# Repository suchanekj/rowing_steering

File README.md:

# Marine Steering System (Buccaneer)

This is a marine steering system designed to track and steer a boat during a rowing outing. It is made up of a cross-platform mobile app built in React Native, along with an Arduino-operated servo designed to control the boat's rudder and a game controller.

The system features three modes:

### 1. Tracking only

This mode tracks your outing without providing any sort of control. Simply line the phone up in the direction of the boat and it will record your outing and useful information like distance and average speed. Past outings can then be reviewed from the history tab.

### 2. Manual mode

In addition to tracking your outing, manual mode allows you to control the boat's rudder from a wireless game controller that can be kept in your hand whilst rowing. Simply connect the servo and controller to the app via bluetooth in the settings tab, and then select manual mode to enable.

### 3. Automatic mode

Lastly, the ultimate goal of the system is to enable fully automated steering. This is a achived by a simple PID controller. The boat's current heading is compared to an average of the river's bearing over the next 100m, weighted by proximity. This forms the error input to a PID controller, which provides a corrective rudder angle output. Simply connect the servo via bluetooth in the settings tab and select automatic mode to enable.

## Screenshots

## Running the app

The app has been built in React Native, a cross-platform framework for developing mobile apps using Javascript.

To work on the app, you'll need to set up a few tools that allow you to run the app on your iOS or Android device. For Android, this involves installing Node and Watchman, followed by the Java Development Kit and Android Studio. See the [docs](https://reactnative.dev/docs/environment-setup) for more details and also for instructions for iOS. Select "React Native CLI Quickstart" rather than "Expo CLI Quickstart". Expo is a set of tools that make React Native development easier, but sadly bluetooth functionality is not yet available in Expo, so we're following the ordinary React Native CLI workflow, sometimes called the "bare workflow".

Once the tools are set up, enable USB debugging on your Android device, connect it via USB and run:

```
npx react-native run-android
```

See the [docs](https://reactnative.dev/docs/running-on-device) for more details and also for instructions for iOS. They also provide [instructions](https://reactnative.dev/docs/signed-apk-android) on building an APK build of the app.

## To do

The functionality of the app is largely complete. It has been tested on Android and the tracking mode works well. The app also correctly scans for and picks up surrounding bluetooth devices. However, manual and automatic modes have yet to be tested in conjunction with the hardware.

In terms of hardware, the servo and game controller must be able to receive and send the following bluetooth messages from the phone:

All bluetooth messages consist of signed 8-bit integers. The servo receives from the phone a rudder angle between -90 and 90, and sends the phone a battery level between 0 and 100. The controller receives from the phone the servo's battery level between 0 and 100, and sends a change in rudder angle between -128 and 127. The phone will add this received value to the current rudder angle to determine the new rudder angle.

The following UUIDs are used for each message. Note that I've come up with new ones, so you'll have to replace the UUIDs used in the current servo code.

```
export const SERVO_SERICE = "802af24b-b40a-488b-b740-4c0405c1f955";
export const BATTERY_LEVEL_CHARACTERISTIC =
  "27468c1f-2915-4b5a-ac6a-6efb97dd764e"; // the servo to phone battery level message (0 to 100)
export const RUDDER_ANGLE_CHARACTERISTIC =
  "948c9983-d637-405b-be86-4565e3c0b7dd"; // the phone to servo rudder angle message (-90 to 90)

export const CONTROLLER_SERVICE = "8be2ecbd-047b-4af5-99fc-ad5a571a99c8";
export const RUDDER_CHANGE_CHARACTERISTIC =
  "1aa10f81-2712-4eb1-a4fc-6c2b0ba74671"; // the controller to phone rudder angle change message (-128 to 127)
export const BATTERY_INFO_CHARACTERISTIC =
  "3a7b1270-435a-4927-86fb-cd135bee2ca5"; // the phone to servo battery level message (0 to 100)

```

## Notes

### Bluetooth device names in the app

The bluetooth library the app uses currently has a bug. When you scan for nearby bluetooth devices, the discovered devices don't have names, only MAC ID addresses. Hopefully this will be fixed in a future release, but for now the app displays the MAC ID addresses of possible devices instead of their names. This isn't ideal but if you keep a note of the MAC ID address of the servo and controller you can connect to the right devices.

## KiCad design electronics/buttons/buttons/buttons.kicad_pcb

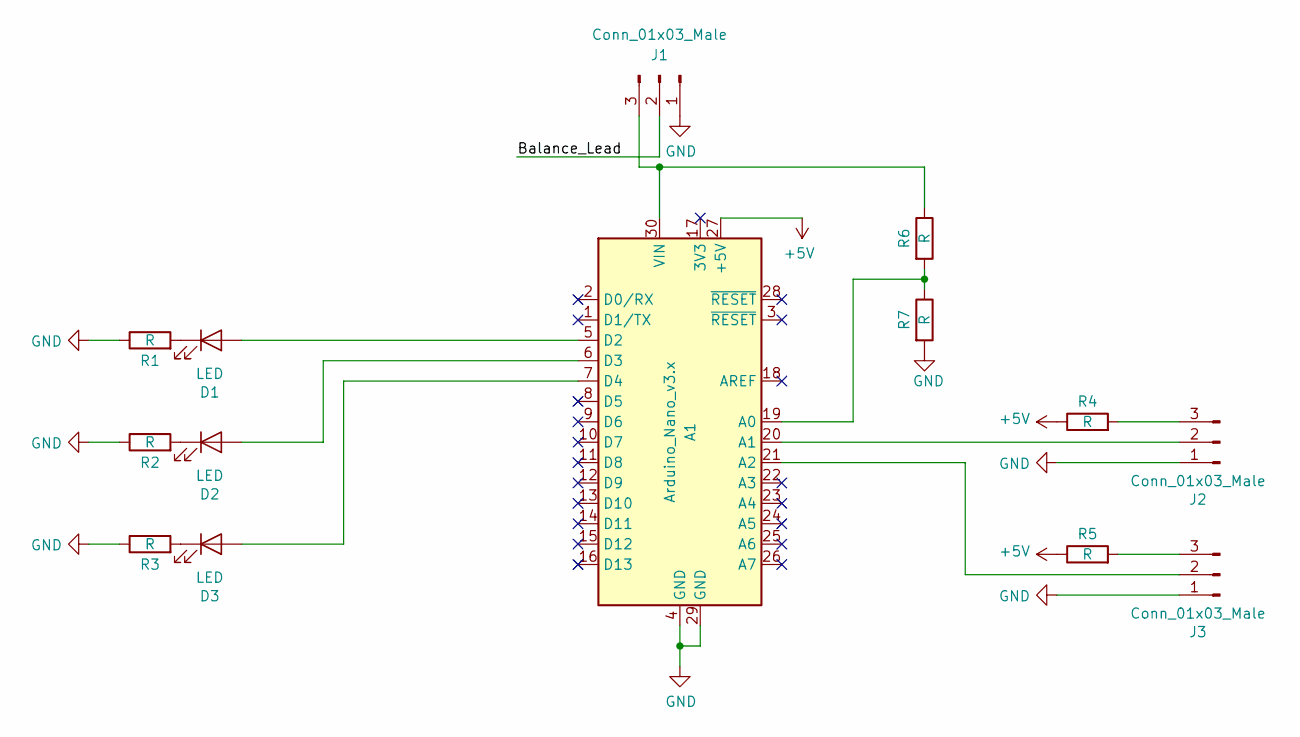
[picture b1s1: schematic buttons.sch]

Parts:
A1: Arduino_Nano_v3.x; NANO_33_Footprint_SMD_Castell
D1, D2, D3: LED; LED_D5.0mm
J1, J2, J3: Conn_01x03_Male; PinHeader_1x03_P2.54mm_Vertical
R1, R2, R3, R4, R5, R6, R7: R; R_1206_3216Metric_Pad1.42x1.75mm_HandSolder

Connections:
+5V: A1.27 (+5V), R4.1, R5.1
/Balance_Lead: J1.2
GND: A1.4 (GND), A1.29 (GND), J1.1, J2.1, J3.1, R1.1, R2.1, R3.1, R7.2
unnamed: A1.5 (D2), D1.2 (A)
unnamed: A1.6 (D3), D2.2 (A)
unnamed: A1.7 (D4), D3.2 (A)
unnamed: A1.19 (A0), R6.2, R7.1
unnamed: A1.20 (A1), J2.2
unnamed: A1.21 (A2), J3.2
unnamed: A1.30 (VIN), J1.3, R6.1
unnamed: D1.1 (K), R1.2
unnamed: D2.1 (K), R2.2
unnamed: D3.1 (K), R3.2
unnamed: J2.3, R4.2
unnamed: J3.3, R5.2

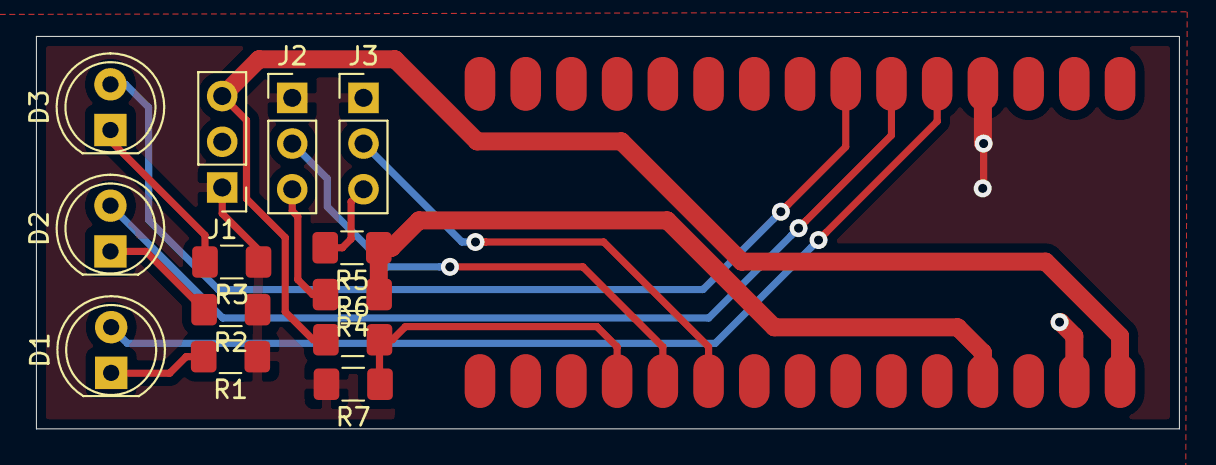
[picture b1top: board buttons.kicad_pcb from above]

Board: 2 copper layers, 63.5 x 21.8 mm, 14 parts (0 on the bottom side), 14 nets.

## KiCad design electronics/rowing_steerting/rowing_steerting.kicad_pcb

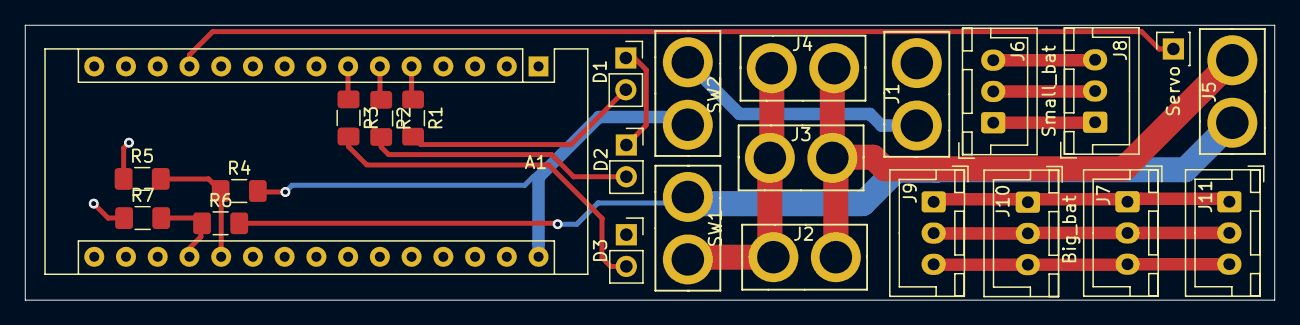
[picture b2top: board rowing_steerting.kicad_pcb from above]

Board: 2 copper layers, 100.0 x 22.0 mm, 25 parts (0 on the bottom side), 20 nets.

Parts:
A1: Arduino_Nano_v3.x; Arduino_Nano
D1, D2, D3: LED; PinSocket_1x02_P2.54mm_Vertical
J1, J2, J3, J4, J5: Conn_01x02_Male; TX30_vertical
J6, J7, J8, J9, J10, J11: Conn_01x03_Female; JST_XH_B3B-XH-A_1x03_P2.50mm_Vertical
R1, R2, R3, R4, R5, R6, R7: R; R_1206_3216Metric_Pad1.42x1.75mm_HandSolder
SW1, SW2: SW_SPST; TX30_vertical
Servo: Conn_01x01_Female; PinSocket_1x01_P2.54mm_Vertical

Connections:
/LED1: A1.7, R3.1
/LED2: A1.6, R2.1
/LED3: A1.5, R1.1
/big_VCC: J2.1, J3.1, J4.1, SW1.2
/big_VCC_switched: J5.1, R6.2, SW1.1
/big_bal1: J7.1, J9.1, J10.1, J11.1
/big_bal2: J7.2, J9.2, J10.2, J11.2
/big_bal3: J7.3, J9.3, J10.3, J11.3
/servo: A1.12, Servo.1
/sm_bal1: J6.1, J8.1
/sm_bal2: J6.2, J8.2
/sm_bal3: J6.3, J8.3
GND: A1.4, A1.29, D1.1, D2.1, D3.1, J1.2, J2.2, J3.2, J4.2, J5.2, R5.1, R7.1
unnamed: A1.19, R6.1, R7.2
unnamed: A1.20, R4.1, R5.2
unnamed: D1.2, R1.2
unnamed: D2.2, R2.2
unnamed: D3.2, R3.2
unnamed: J1.1, SW2.1
VCC: A1.30, R4.2, SW2.2

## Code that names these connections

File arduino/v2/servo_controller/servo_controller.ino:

#include <ArduinoBLE.h>
#include "Servo.h"

#define LED1 2
#define LED2 3
// LED3 is green but doesn't work... :-(
#define LED3 4

#define BIG_V_READ A0
#define SMALL_V_READ A1

#define SERVO_PIN 9

BLEService steeringService("19B10000-E8F2-537E-4F6C-D104768A1214"); // BLE LED Service
// BLE LED Switch Characteristic - custom 128-bit UUID, read and writable by central
BLEByteCharacteristic switchCharacteristic("19B10001-E8F2-537E-4F6C-D104768A1214", BLERead | BLEWrite);

Servo myservo;
float small_v, big_v;

void setup() {
  Serial.begin(9600);
  myservo.attach(SERVO_PIN);
  myservo.write(90);

  pinMode(LED1, OUTPUT);
  pinMode(LED2, OUTPUT);
  pinMode(LED3, OUTPUT);
  
  digitalWrite(LED1, HIGH);
  digitalWrite(LED2, HIGH);
  digitalWrite(LED3, HIGH);
  
  pinMode(BIG_V_READ, INPUT);
  pinMode(SMALL_V_READ, INPUT);

  BLE.begin();

  BLE.setLocalName("Steering");
  BLE.setAdvertisedService(steeringService);

  // add the characteristic to the service
  steeringService.addCharacteristic(switchCharacteristic);
  BLE.addService(steeringService);
  switchCharacteristic.writeValue(0);
  BLE.advertise();
}

void loop() {
  // put your main code here, to run repeatedly:
  big_v = analogRead(BIG_V_READ) * 10.0 / 1024;
  small_v = analogRead(SMALL_V_READ) * 10.0 / 1024;

  Serial.print(big_v);
  Serial.print("V \t");
  Serial.print(small_v);
  Serial.println("V");

  BLEDevice central = BLE.central();

  // if a central is connected to peripheral:
  if (central) {
    Serial.print("Connected to central: ");
    // print the central's MAC address:
    Serial.println(central.address());

    // while the central is still connected to peripheral:
    while (central.connected()) {
       byte val = 255;
      // if the remote device wrote to the characteristic,
      // use the value to control the LED:
      if (switchCharacteristic.written()) {
        val = switchCharacteristic.value();
        if(val <= 180) {
          myservo.write(val);
        }
      }
      big_v = analogRead(BIG_V_READ) * 6.6 / 1024;
      small_v = analogRead(SMALL_V_READ) * 6.6 / 1024;
      Serial.print(val);
      Serial.print("  \t");
      Serial.print(big_v);
      Serial.print("V \t");
      Serial.print(small_v);
      Serial.println("V");
    }

    // when the central disconnects, print it out:
    Serial.print(F("Disconnected from central: "));
    Serial.println(central.address());
  }
}

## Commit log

2019-02-02 First version of the model
2019-02-17 Fix position of rudder cable and boat width, add a new servo, a new battery, switches, case window and the phone holder.
2019-02-19 Add phone holder clips and screw holes to secure the case together
2019-02-22 Edit case and holders, add fabrication files
2020-01-20 Final model, some arduino code, some electronics schematics
2020-01-23 update schematic
2020-01-25 added gerbers rowing_steering board
2020-03-18 Added buttons board
2020-03-19 change button pcb layout. Added fab files
2020-03-19 fix erros in the model
2020-05-02 Initial React Native project with bare workflow to support bluetooth
2020-05-09 v2 arduino code
2020-06-21 App layout with tabs and map view
2020-07-02 Track location and save outing data to local storage
2020-07-14 Trace on live map and display previous outings
2020-07-16 Implemented bluetooth communication and device handling
2020-07-16 Display heading, rudder angle and speed during tracking
2020-07-16 Added outing information, button to delete past outings and fixed location subscription removal
2020-07-20 Bump lodash from 4.17.15 to 4.17.19 in /app
    Bumps [lodash](https://github.com/lodash/lodash) from 4.17.15 to 4.17.19.
    - [Release notes](https://github.com/lodash/lodash/releases)
    - [Commits](https://github.com/lodash/lodash/compare/4.17.15...4.17.19)
2020-08-14 Updated rudder angle and battery level communication
2020-08-15 Implemented an automatic control system based on weighted river bearings
2020-08-15 Prepared for Android build
2020-08-15 Updated peripheral scanning and status card
2021-03-31 Bump y18n from 3.2.1 to 3.2.2 in /app
    Bumps [y18n](https://github.com/yargs/y18n) from 3.2.1 to 3.2.2.
    - [Release notes](https://github.com/yargs/y18n/releases)
    - [Changelog](https://github.com/yargs/y18n/blob/master/CHANGELOG.md)
    - [Commits](https://github.com/yargs/y18n/commits)
2021-05-07 Bump ua-parser-js from 0.7.21 to 0.7.28 in /app
    Bumps [ua-parser-js](https://github.com/faisalman/ua-parser-js) from 0.7.21 to 0.7.28.
    - [Release notes](https://github.com/faisalman/ua-parser-js/releases)
    - [Commits](https://github.com/faisalman/ua-parser-js/compare/0.7.21...0.7.28)
2021-05-09 Bump url-parse from 1.4.7 to 1.5.1 in /app
    Bumps [url-parse](https://github.com/unshiftio/url-parse) from 1.4.7 to 1.5.1.
    - [Release notes](https://github.com/unshiftio/url-parse/releases)
    - [Commits](https://github.com/unshiftio/url-parse/compare/1.4.7...1.5.1)
2021-05-11 Bump lodash from 4.17.15 to 4.17.21 in /app
    Bumps [lodash](https://github.com/lodash/lodash) from 4.17.15 to 4.17.21.
    - [Release notes](https://github.com/lodash/lodash/releases)
    - [Commits](https://github.com/lodash/lodash/compare/4.17.15...4.17.21)
2021-05-11 Bump hosted-git-info from 2.8.8 to 2.8.9 in /app
    Bumps [hosted-git-info](https://github.com/npm/hosted-git-info) from 2.8.8 to 2.8.9.
    - [Release notes](https://github.com/npm/hosted-git-info/releases)
    - [Changelog](https://github.com/npm/hosted-git-info/blob/v2.8.9/CHANGELOG.md)
    - [Commits](https://github.com/npm/hosted-git-info/compare/v2.8.8...v2.8.9)
2021-05-26 Bump browserslist from 4.12.0 to 4.16.6 in /app
    Bumps [browserslist](https://github.com/browserslist/browserslist) from 4.12.0 to 4.16.6.
    - [Release notes](https://github.com/browserslist/browserslist/releases)
    - [Changelog](https://github.com/browserslist/browserslist/blob/main/CHANGELOG.md)
    - [Commits](https://github.com/browserslist/browserslist/compare/4.12.0...4.16.6)
2021-07-20 Bump react-native from 0.61.4 to 0.62.3 in /app
    Bumps [react-native](https://github.com/facebook/react-native) from 0.61.4 to 0.62.3.
    - [Release notes](https://github.com/facebook/react-native/releases)
    - [Changelog](https://github.com/facebook/react-native/blob/main/Releases.md)
    - [Commits](https://github.com/facebook/react-native/compare/v0.61.4...v0.62.3)
    ---
    updated-dependencies:
2021-08-12 Bump path-parse from 1.0.6 to 1.0.7 in /app
    Bumps [path-parse](https://github.com/jbgutierrez/path-parse) from 1.0.6 to 1.0.7.
    - [Release notes](https://github.com/jbgutierrez/path-parse/releases)
    - [Commits](https://github.com/jbgutierrez/path-parse/commits/v1.0.7)
    ---
    updated-dependencies:
    - dependency-name: path-parse
2021-09-21 Bump tmpl from 1.0.4 to 1.0.5 in /app
    Bumps [tmpl](https://github.com/daaku/nodejs-tmpl) from 1.0.4 to 1.0.5.
    - [Release notes](https://github.com/daaku/nodejs-tmpl/releases)
    - [Commits](https://github.com/daaku/nodejs-tmpl/commits/v1.0.5)
    ---
    updated-dependencies:
    - dependency-name: tmpl
2021-10-06 Bump url-parse from 1.4.7 to 1.5.3 in /app
    Bumps [url-parse](https://github.com/unshiftio/url-parse) from 1.4.7 to 1.5.3.
    - [Release notes](https://github.com/unshiftio/url-parse/releases)
    - [Commits](https://github.com/unshiftio/url-parse/compare/1.4.7...1.5.3)
    ---
    updated-dependencies:
    - dependency-name: url-parse
2022-02-19 Bump url-parse from 1.4.7 to 1.5.7 in /app
    Bumps [url-parse](https://github.com/unshiftio/url-parse) from 1.4.7 to 1.5.7.
    - [Release notes](https://github.com/unshiftio/url-parse/releases)
    - [Commits](https://github.com/unshiftio/url-parse/compare/1.4.7...1.5.7)
    ---
    updated-dependencies:
    - dependency-name: url-parse
2022-02-27 Bump url-parse from 1.4.7 to 1.5.10 in /app
    Bumps [url-parse](https://github.com/unshiftio/url-parse) from 1.4.7 to 1.5.10.
    - [Release notes](https://github.com/unshiftio/url-parse/releases)
    - [Commits](https://github.com/unshiftio/url-parse/compare/1.4.7...1.5.10)
    ---
    updated-dependencies:
    - dependency-name: url-parse
2022-03-02 Bump plist from 3.0.1 to 3.0.4 in /app
    Bumps [plist](https://github.com/TooTallNate/node-plist) from 3.0.1 to 3.0.4.
    - [Release notes](https://github.com/TooTallNate/node-plist/releases)
    - [Changelog](https://github.com/TooTallNate/plist.js/blob/master/History.md)
    - [Commits](https://github.com/TooTallNate/node-plist/commits)
    ---
    updated-dependencies:
2022-03-26 Bump minimist from 1.2.5 to 1.2.6 in /app
    Bumps [minimist](https://github.com/substack/minimist) from 1.2.5 to 1.2.6.
    - [Release notes](https://github.com/substack/minimist/releases)
    - [Commits](https://github.com/substack/minimist/compare/1.2.5...1.2.6)
    ---
    updated-dependencies:
    - dependency-name: minimist
2022-04-29 Bump async from 2.6.3 to 2.6.4 in /app
    Bumps [async](https://github.com/caolan/async) from 2.6.3 to 2.6.4.
    - [Release notes](https://github.com/caolan/async/releases)
    - [Changelog](https://github.com/caolan/async/blob/v2.6.4/CHANGELOG.md)
    - [Commits](https://github.com/caolan/async/compare/v2.6.3...v2.6.4)
    ---
    updated-dependencies:
2022-06-02 Bump simple-plist from 1.1.0 to 1.3.1 in /app
    Bumps [simple-plist](https://github.com/wollardj/simple-plist) from 1.1.0 to 1.3.1.
    - [Release notes](https://github.com/wollardj/simple-plist/releases)
    - [Commits](https://github.com/wollardj/simple-plist/compare/1.1.0...v1.3.1)
    ---
    updated-dependencies:
    - dependency-name: simple-plist
2022-10-12 Bump xmldom and plist in /app
    Removes [xmldom](https://github.com/xmldom/xmldom). It's no longer used after updating ancestor dependency [plist](https://github.com/TooTallNate/node-plist). These dependencies need to be updated to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
    Removes `xmldom`
    Updates `plist` from 3.0.1 to 3.0.6
    - [Release notes](https://github.com/TooTallNate/node-plist/releases)
    - [Changelog](https://github.com/TooTallNate/plist.js/blob/master/History.md)
    - [Commits](https://github.com/TooTallNate/node-plist/commits)
2022-10-20 Bump react-native-reanimated from 1.13.0 to 2.10.0 in /app
    Bumps [react-native-reanimated](https://github.com/software-mansion/react-native-reanimated) from 1.13.0 to 2.10.0.
    - [Release notes](https://github.com/software-mansion/react-native-reanimated/releases)
    - [Commits](https://github.com/software-mansion/react-native-reanimated/compare/1.13.0...2.10.0)
    ---
    updated-dependencies:
    - dependency-name: react-native-reanimated
2022-12-06 Bump decode-uri-component from 0.2.0 to 0.2.2 in /app
    Bumps [decode-uri-component](https://github.com/SamVerschueren/decode-uri-component) from 0.2.0 to 0.2.2.
    - [Release notes](https://github.com/SamVerschueren/decode-uri-component/releases)
    - [Commits](https://github.com/SamVerschueren/decode-uri-component/compare/v0.2.0...v0.2.2)
    ---
    updated-dependencies:
    - dependency-name: decode-uri-component
2022-12-06 Bump qs from 6.5.2 to 6.5.3 in /app
    Bumps [qs](https://github.com/ljharb/qs) from 6.5.2 to 6.5.3.
    - [Release notes](https://github.com/ljharb/qs/releases)
    - [Changelog](https://github.com/ljharb/qs/blob/main/CHANGELOG.md)
    - [Commits](https://github.com/ljharb/qs/compare/v6.5.2...v6.5.3)
    ---
    updated-dependencies:
